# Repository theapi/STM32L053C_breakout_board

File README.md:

# STM32L053C_breakout_board
Breakout board for the STM32L053C 48 pin mcu

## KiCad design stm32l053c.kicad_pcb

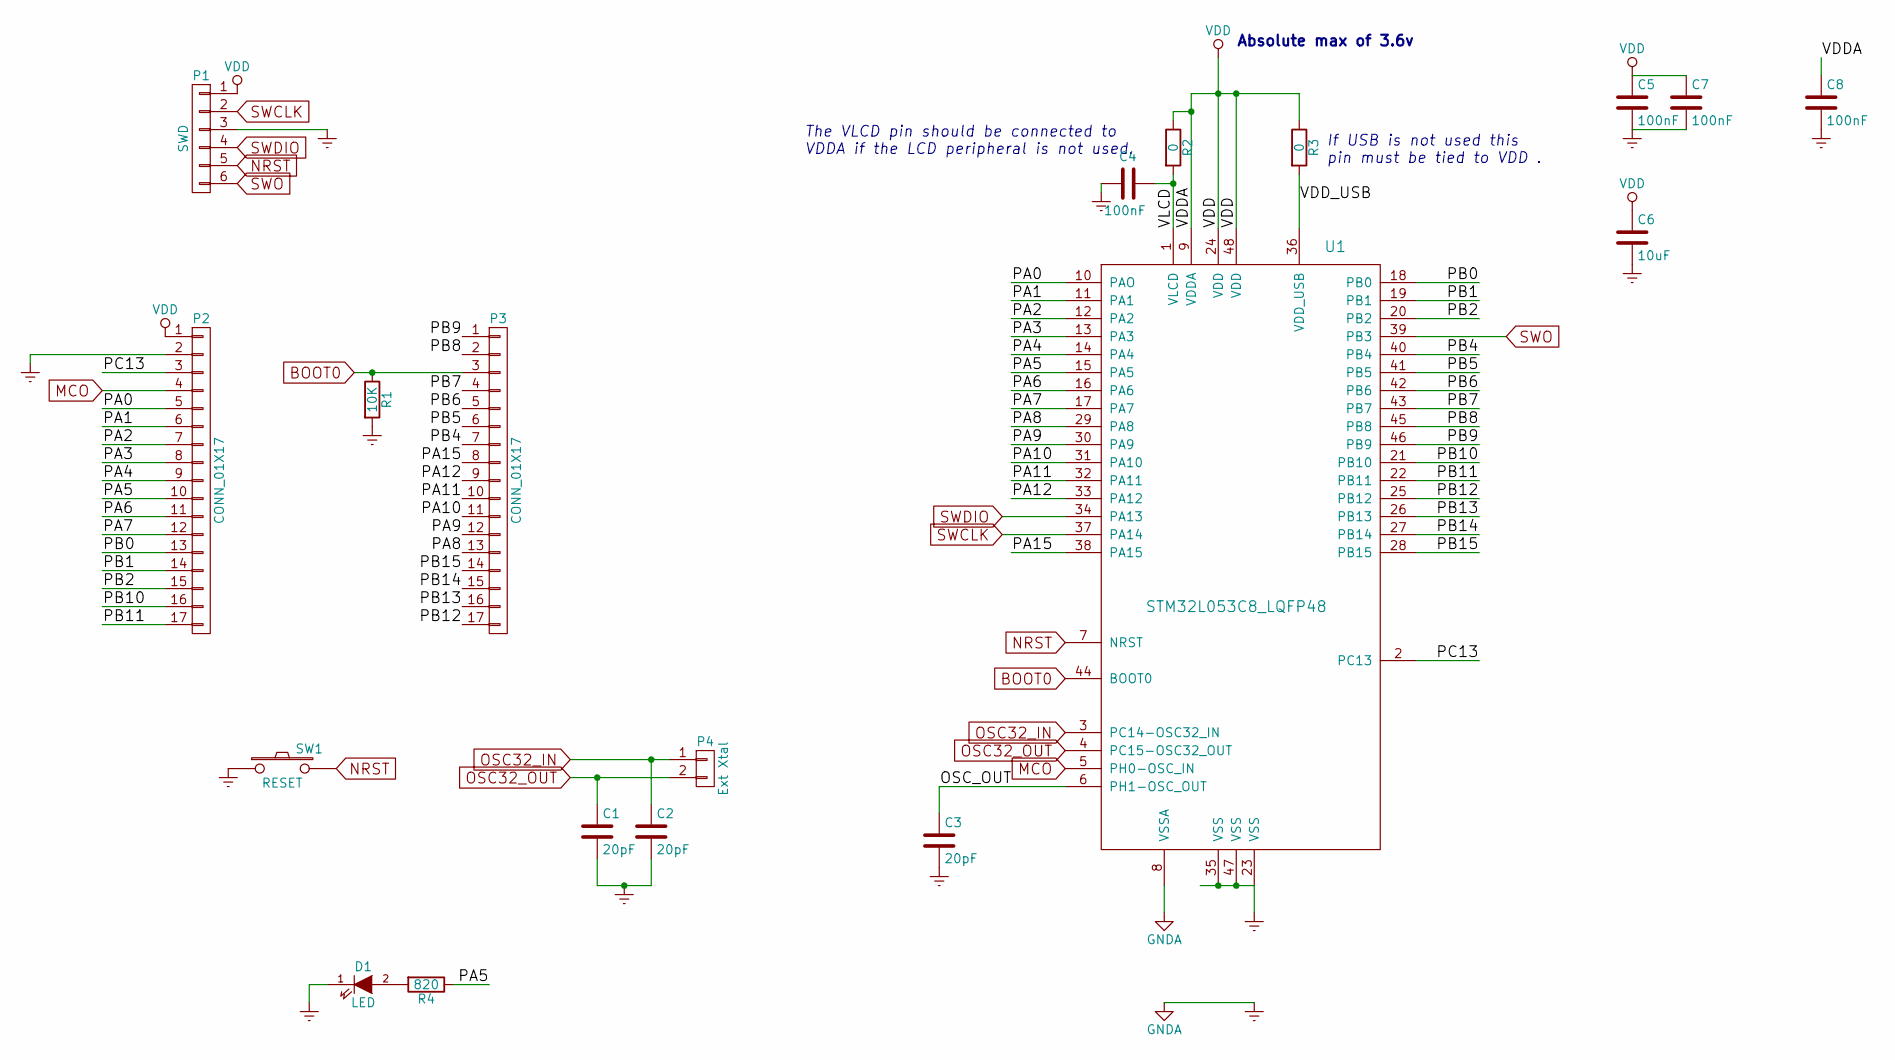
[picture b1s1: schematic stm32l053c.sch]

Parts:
C1, C2, C3: 20pF; C_0805_HandSoldering
C4, C5, C7, C8: 100nF; C_0805_HandSoldering
C6: 10uF; C_0805_HandSoldering
D1: LED; LED_0805
P1: SWD; Pin_Header_Straight_1x06
P2, P3: CONN_01X17; Pin_Header_Straight_1x17
P4: Ext Xtal; Crystal_SMD_0603_2Pads_obsolete
R1: 10K; R_0805_HandSoldering
R2, R3: 0; R_0402
R4: 820; R_0805_HandSoldering
SW1: RESET; SW_PUSH_6mm
U1: STM32L053C8_LQFP48; LQFP-48_7x7mm_Pitch0.5mm

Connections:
/OSC_OUT: C3.1, U1.6 (PH1-OSC_OUT)
/PA0: P2.5, U1.10 (PAO)
/PA1: P2.6, U1.11 (PA1)
/PA2: P2.7, U1.12 (PA2)
/PA3: P2.8, U1.13 (PA3)
/PA4: P2.9, U1.14 (PA4)
/PA5: P2.10, R4.1, U1.15 (PA5)
/PA6: P2.11, U1.16 (PA6)
/PA7: P2.12, U1.17 (PA7)
/PA8: P3.13, U1.29 (PA8)
/PA9: P3.12, U1.30 (PA9)
/PA10: P3.11, U1.31 (PA10)
/PA11: P3.10, U1.32 (PA11)
/PA12: P3.9, U1.33 (PA12)
/PA15: P3.8, U1.38 (PA15)
/PB0: P2.13, U1.18 (PB0)
/PB1: P2.14, U1.19 (PB1)
/PB2: P2.15, U1.20 (PB2)
/PB4: P3.7, U1.40 (PB4)
/PB5: P3.6, U1.41 (PB5)
/PB6: P3.5, U1.42 (PB6)
/PB7: P3.4, U1.43 (PB7)
/PB8: P3.2, U1.45 (PB8)
/PB9: P3.1, U1.46 (PB9)
/PB10: P2.16, U1.21 (PB10)
/PB11: P2.17, U1.22 (PB11)
/PB12: P3.17, U1.25 (PB12)
/PB13: P3.16, U1.26 (PB13)
/PB14: P3.15, U1.27 (PB14)
/PB15: P3.14, U1.28 (PB15)
/PC13: P2.3, U1.2 (PC13)
/VDD_USB: R3.2, U1.36 (VDD_USB)
/VLCD: C4.2, R2.2, U1.1 (VLCD)
BOOT0: P3.3, R1.1, U1.44 (BOOT0)
Earth: C1.2, C2.2, C3.2, C4.1, C5.2, C6.2, C7.2, C8.2, D1.1 (K), P1.3, P2.2, R1.2, SW1.1, U1.8 (VSSA), U1.23 (VSS), U1.35 (VSS), U1.47 (VSS); also elsewhere on the board
MCO: P2.4, U1.5 (PH0-OSC_IN)
NRST: P1.5, SW1.2, U1.7 (NRST); also elsewhere on the board
unnamed: D1.2 (A), R4.2
OSC32_IN: C2.1, P4.1, U1.3 (PC14-OSC32_IN)
OSC32_OUT: C1.1, P4.2, U1.4 (PC15-OSC32_OUT)
SWCLK: P1.2, U1.37 (PA14)
SWDIO: P1.4, U1.34 (PA13)
SWO: P1.6, U1.39 (PB3)
VDD: C5.1, C6.1, C7.1, C8.1, P1.1, P2.1, R2.1, R3.1, U1.9 (VDDA), U1.24 (VDD), U1.48 (VDD)

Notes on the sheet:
The VLCD pin should be connected to VDDA if the LCD peripheral is not used.
If USB is not used this pin must be tied to VDD .
Absolute max of 3.6v

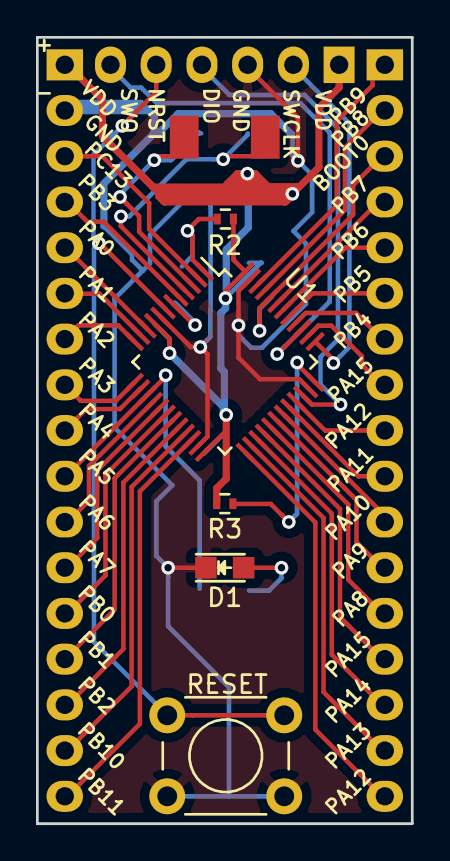
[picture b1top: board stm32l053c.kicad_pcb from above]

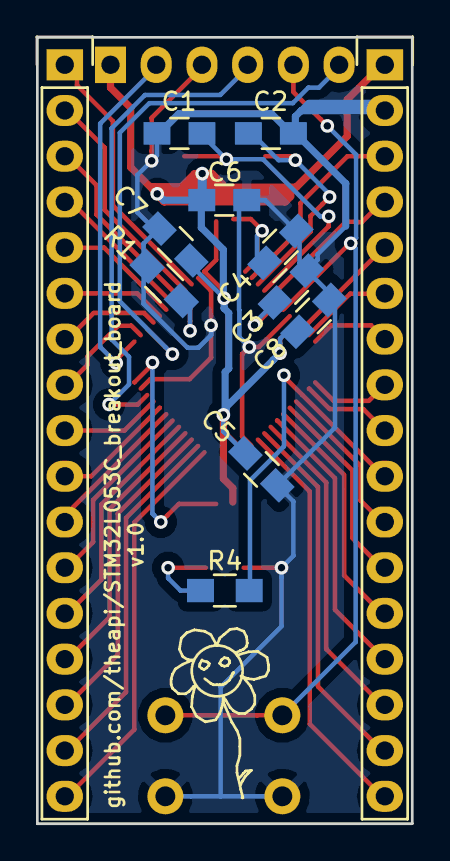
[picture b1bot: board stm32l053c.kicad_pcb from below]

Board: 2 copper layers, 20.8 x 43.7 mm, 19 parts (12 on the bottom side), 44 nets.

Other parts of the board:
RESET: RESET; SW_PUSH_6mm

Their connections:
Earth: RESET.1; also elsewhere on the board
NRST: RESET.2; also elsewhere on the board

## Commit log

2016-10-18 Schematic & layout
2016-10-18 Solder bridges
2016-10-18 Extra ground
2016-10-19 LED on "D13"
2016-10-25 Silkscreen labels
2016-10-26 Logos
2016-10-26 Soldermask clearance
2016-10-26 Gerbers
2016-10-27 Renders of the board
2016-11-17 Correctd labels for PB12 to PB15
2016-11-17 Schematic pdf
2016-11-17 Fixed the label for MCO
